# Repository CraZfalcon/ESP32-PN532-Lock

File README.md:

# ESP32-PN532-Lock
A door lock that uses a XIAO ESP32C3 microcontroller and a PN532 card reader to create an API call and activate an actuator

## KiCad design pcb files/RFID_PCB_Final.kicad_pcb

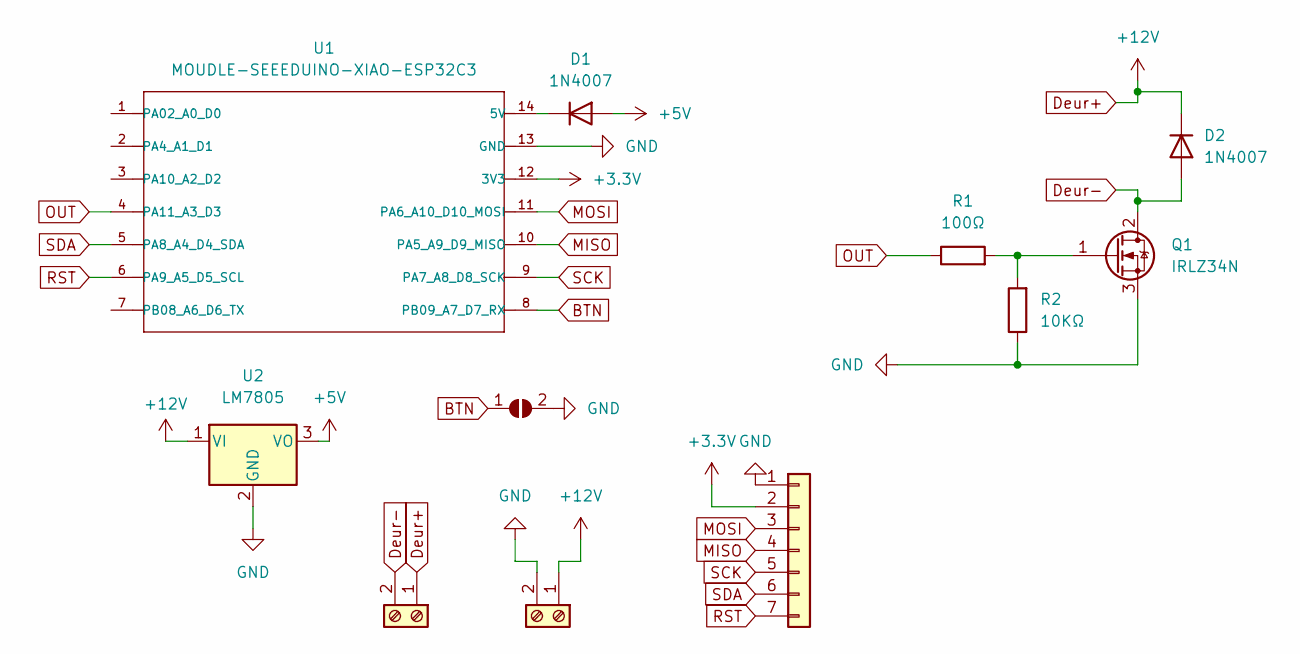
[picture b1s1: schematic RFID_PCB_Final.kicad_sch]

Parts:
D1, D2: 1N4007; D_DO-41_SOD81_P10.16mm_Horizontal
J1, J2: Screw_Terminal_01x02; TerminalBlock_bornier-2_P5.08mm
J9: Conn_01x07; PinSocket_1x07_P2.54mm_Vertical
JP1: SolderJumper_2_Open; SolderJumper-2_P1.3mm_Open_Pad1.0x1.5mm
Q1: IRLZ34N; TO-220-3_Vertical
R1: 100Ω; R_Axial_DIN0204_L3.6mm_D1.6mm_P7.62mm_Horizontal
R2: 10KΩ; R_Axial_DIN0204_L3.6mm_D1.6mm_P7.62mm_Horizontal
U1: MOUDLE-SEEEDUINO-XIAO-ESP32C3; MOUDLE14P-SMD-2.54-21X17.8MM-HOLE
U2: LM7805; TO-220-3_Vertical

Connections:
+3.3V: J9.2, U1.12 (3V3)
+5V: D1.2 (A), U2.3 (VO)
BTN: JP1.1 (A), U1.8 (PB09_A7_D7_RX)
Deur+: D2.1 (K), J1.1, J2.1, U2.1 (VI)
Deur-: D2.2 (A), J2.2, Q1.2 (D)
GND: J1.2, J9.1, JP1.2 (B), Q1.3 (S), R2.1, U1.13 (GND), U2.2 (GND)
MISO: J9.4, U1.10 (PA5_A9_D9_MISO)
MOSI: J9.3, U1.11 (PA6_A10_D10_MOSI)
unnamed: D1.1 (K), U1.14 (5V)
unnamed: Q1.1 (G), R1.2, R2.2
OUT: R1.1, U1.4 (PA11_A3_D3)
RST: J9.7, U1.6 (PA9_A5_D5_SCL)
SCK: J9.5, U1.9 (PA7_A8_D8_SCK)
SDA: J9.6, U1.5 (PA8_A4_D4_SDA)

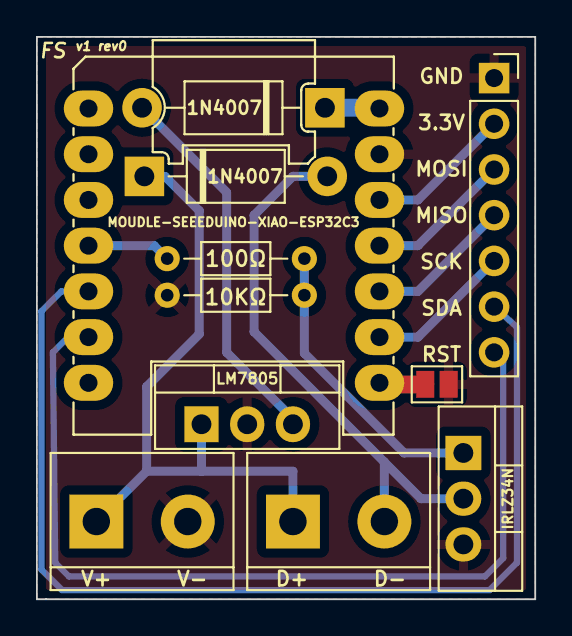
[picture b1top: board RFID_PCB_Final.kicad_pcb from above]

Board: 2 copper layers, 27.7 x 31.2 mm, 11 parts (0 on the bottom side), 14 nets.

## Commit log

2023-06-26 V1
    First commit
2023-06-26 V1.1
    removed libraries
2023-06-26 v1.2
    Modification test
2023-07-04 V1.3
    Added libraries locally to ensure reliability
2023-07-04 V1.4
    Added libraries locally to ensure stability.... 2nd attempt
2023-07-04 V1.5
    Added libraries locally to ensure stability... 3rd attempt
2023-07-04 V1.6
    Added .pio folder
2023-07-04 V1.7
    Added a SPIFFS formatting script and removed .pio and .vscode folders
2023-07-04 V1.8
    Added pcb files
2023-07-04 V1.8.1
    .pio and .vscode fix
2023-07-04 V1.8.2
    .pio and .vscode fix pt2
2023-07-04 V1.8.3
    Removing empty folders
2023-10-04 V1.8.4
    Library update for upcoming features
2023-12-04 V2.0
    Code redesign & possible freeze fix
2023-12-19 V2.0.1
    Attempt at fixing DNS error and ssl failure
